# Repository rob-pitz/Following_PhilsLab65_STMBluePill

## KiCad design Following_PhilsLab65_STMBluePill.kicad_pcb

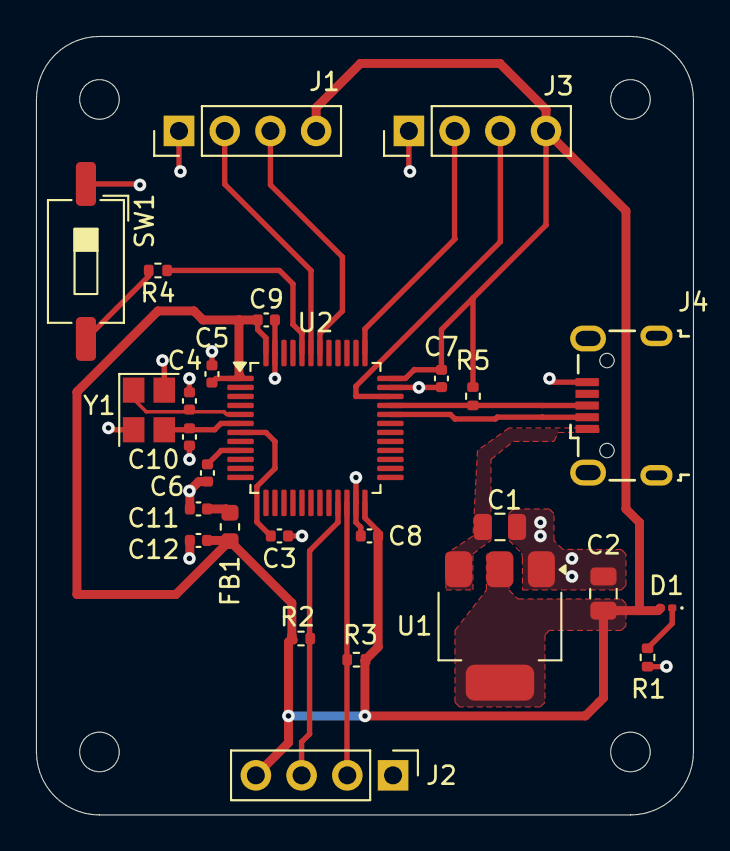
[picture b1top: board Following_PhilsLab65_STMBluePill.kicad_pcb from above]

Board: 2 copper layers, 36.5 x 43.2 mm, 31 parts (0 on the bottom side), 18 nets.

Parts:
C1, C2: 22u; C_0805_2012Metric
C3, C5, C7, C8, C9: 100n; C_0402_1005Metric
C4, C6: 10p; C_0402_1005Metric
C10: 10n; C_0402_1005Metric
C11, C12: 1u; C_0402_1005Metric
D1: RED; LED_0201_0603Metric
FB1: 120R; L_0603_1608Metric
H1, H2, H3, H4: MountingHole; MountingHole_2.2mm_M2
J1, J2, J3: Conn_01x04_Pin; PinHeader_1x04_P2.54mm_Vertical
J4: USB_B_Micro; USB_Micro-B_Wuerth_629105150521
R1, R2, R3: 1k5; R_0402_1005Metric
R4: 10k; R_0402_1005Metric
R5: 1K5; R_0402_1005Metric
SW1: SW_SPDT; SW_DIP_SPSTx01_Slide_6.7x4.1mm_W8.61mm_P2.54mm_LowProfile
U1: AMS1117-3.3; SOT-223-3_TabPin2
U2: STM32F103C8Tx; LQFP-48_7x7mm_P0.5mm
Y1: 16MHz; Crystal_SMD_3225-4Pin_3.2x2.5mm

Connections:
+3.3V: C2.1, C5.1, C7.1, C8.1, C9.1, C12.1, D1.2 (A), FB1.2, J1.4, J2.4, J3.4, R2.1, R3.1, R5.1, U1.2 (VO), U2.1 (VBAT), U2.24 (VDD), U2.36 (VDD), U2.48 (VDD)
+3.3VA: C10.2, C11.1, FB1.1, U2.9 (VDDA)
/BOOT0: R4.2, U2.44 (BOOT0)
/HSE_IN: C4.1, U2.5 (PD0), Y1.1
/HSE_OUT: C6.1, U2.6 (PD1), Y1.3
/I2C2_SCL: J2.3, R2.2, U2.21 (PB10)
/I2C2_SDA: J2.2, R3.2, U2.22 (PB11)
/NRST: C3.1, U2.7 (NRST)
/PWR_LED_K: D1.1 (K), R1.1
/SWCLK: J3.2, U2.37 (PA14)
/SWDIO: J3.3, U2.34 (PA13)
/SW_BOOT0: R4.1, SW1.2 (B)
/USART1_RX: J1.2, U2.43 (PB7)
/USART1_TX: J1.3, U2.42 (PB6)
/USB_D+: J4.3 (D+), R5.2, U2.33 (PA12)
/USB_D-: J4.2 (D-), U2.32 (PA11)
GND: C1.2, C2.2, C3.2, C4.2, C5.2, C6.2, C7.2, C8.2, C9.2, C10.1, C11.2, C12.2, J1.1, J2.1, J3.1, J4.5 (GND), R1.2, SW1.1 (A), U1.1 (GND), U2.8 (VSSA), U2.23 (VSS), U2.35 (VSS), U2.47 (VSS), Y1.2, Y1.4
VBUS: C1.1, J4.1 (VBUS), U1.3 (VI)

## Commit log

2025-06-18 refactor
